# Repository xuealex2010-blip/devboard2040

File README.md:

# A custom devboard based on the RP2040
This is my very own design of a devboard, it is very similar to the Rasberry Pi Pico, I created it to learn more about microcontrollers, it is also my first design with a microcontroller.

## Overview
This devboard uses an RP2040, it exposes 28 total GPIO pins.

The devboard has 2 LEDs on it, a red one to signal the power connection, and a green one that can be controlled with GPIO 25.

It uses a USB-C connector instead off the Micro USB connector on the official one. And it has the necessary CC1 and CC2 resistors so it can be connected to a USB C port.

The external pins are also labeled, so that you don't always need to reference a pinout when working on projects.

Details with the source files can be previewed with KiCanvas: 

[https://kicanvas.org/?repo=https%3A%2F%2Fgithub.com%2Fxuealex2010-blip%2Fdevboard2040%2Ftree%2Fmain%2FPCB](url)

### Fabrication
The files necessary to manufacture your own version of this board can be found in the production folder, it has all of the necessary files and more, formatted for JLC PCB.
If you use another vendor, you may need to use the source files from the PCB folder to create your own production files.

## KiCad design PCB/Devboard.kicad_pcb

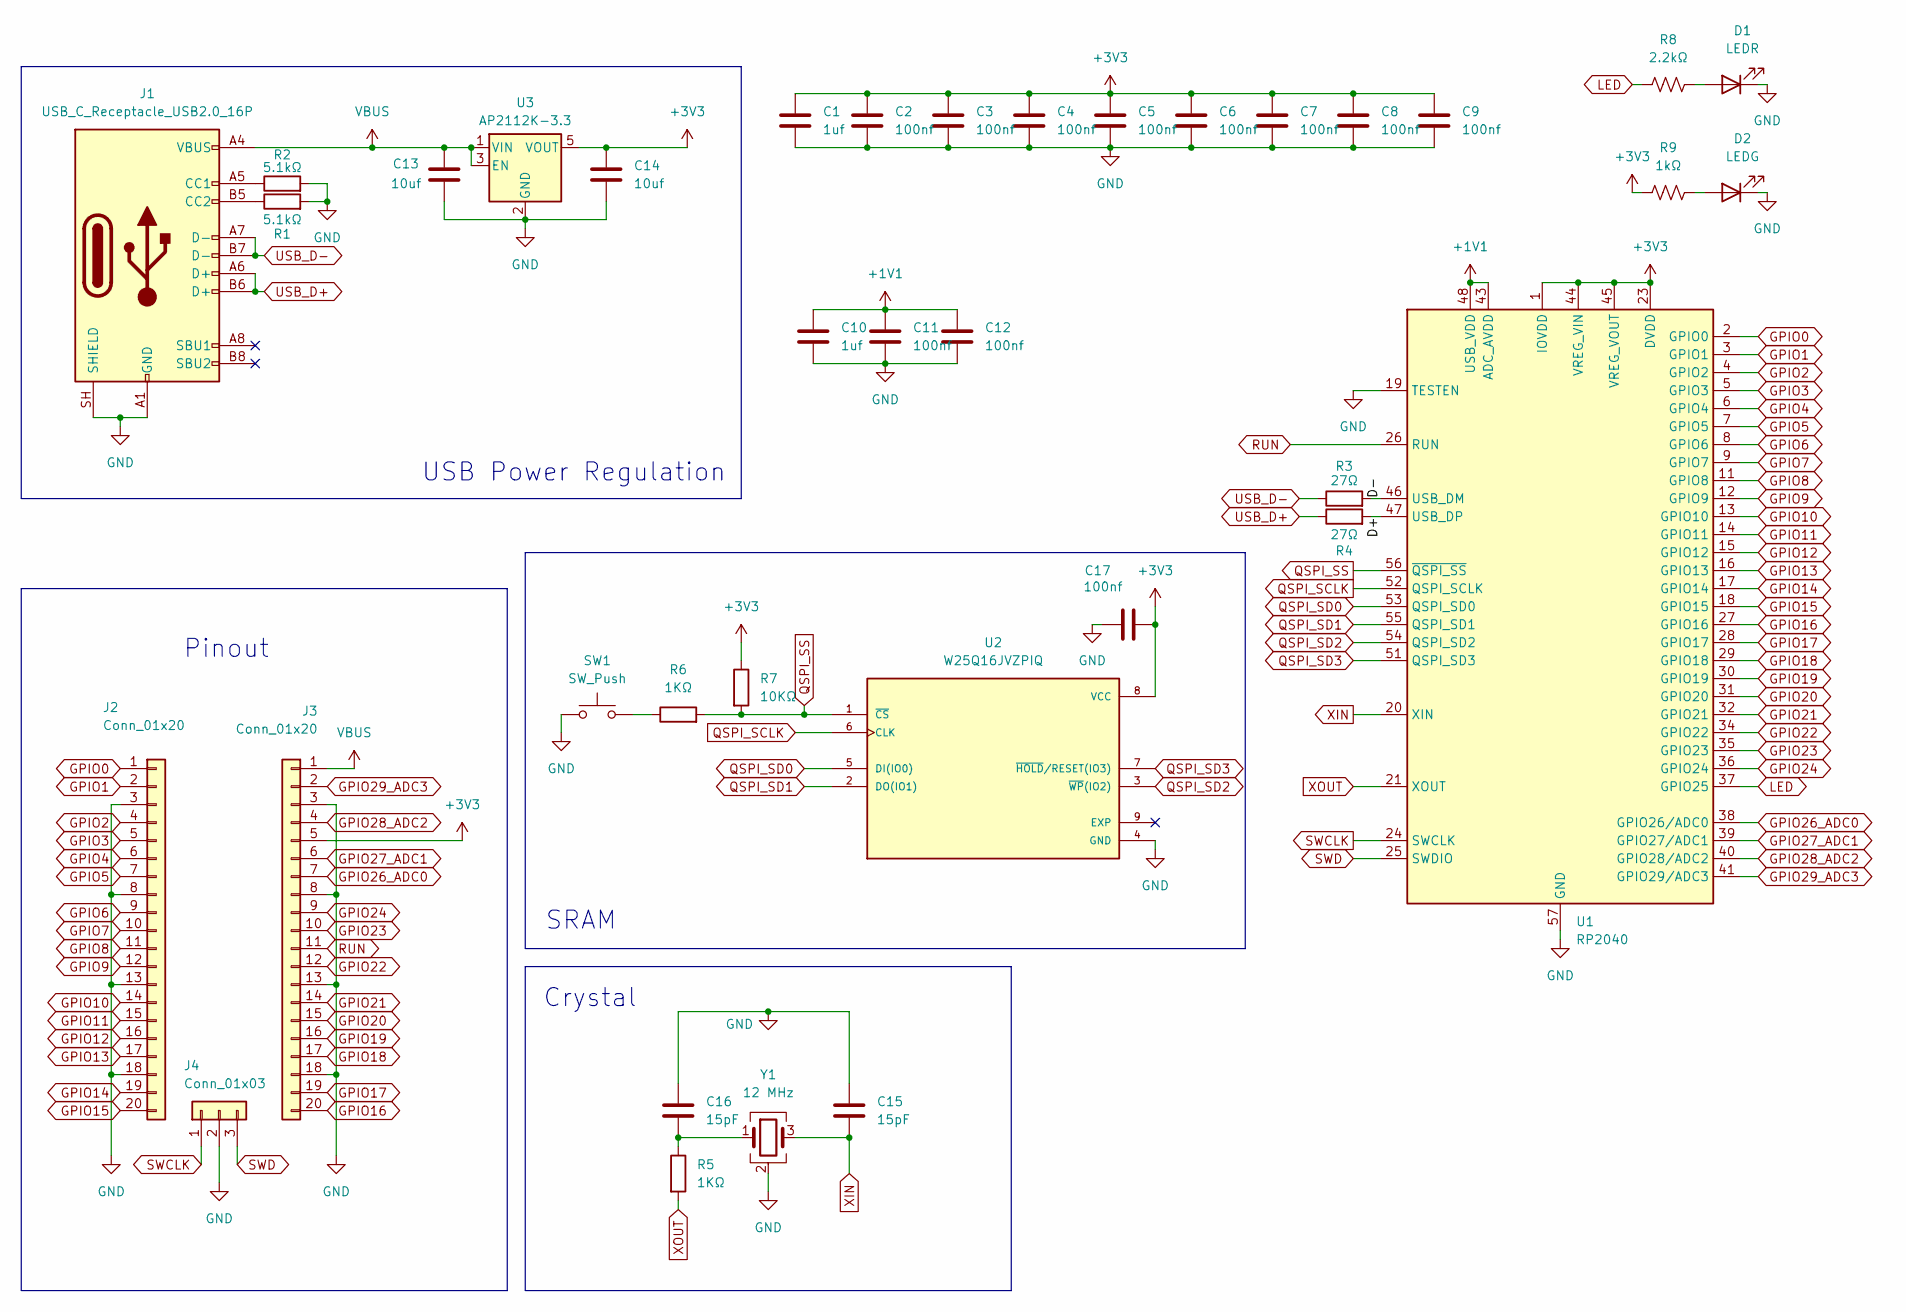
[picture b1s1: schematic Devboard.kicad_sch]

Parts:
C1, C10: 1uf; C_0402_1005Metric
C2, C3, C4, C5, C6, C7, C8, C9, C11, C12, C17: 100nf; C_0402_1005Metric
C13, C14: 10uf; C_0603_1608Metric
C15, C16: 15pF; C_0402_1005Metric
D1: LEDR; LED_0603_1608Metric
D2: LEDG; LED_0805_2012Metric
J1: USB_C_Receptacle_USB2.0_16P; USB_C_NEW(IDK)
J2, J3: Conn_01x20; PinHeader_1x20_P2.54mm_Vertical
J4: Conn_01x03; PinHeader_1x03_P2.54mm_Vertical
R1, R2: 5.1kΩ; R_0402_1005Metric
R3, R4: 27Ω; R_0402_1005Metric
R5, R6: 1KΩ; R_0402_1005Metric
R7: 10KΩ; R_0402_1005Metric
R8: 2.2kΩ; R_0402_1005Metric
R9: 1kΩ; R_0402_1005Metric
SW1: SW_Push; SW_Push_SPST_NO_Alps_SKRK
U1: RP2040; QFN-56-1EP_7x7mm_P0.4mm_EP3.2x3.2mm
U2: W25Q16JVZPIQ; Winbond_USON-8-1EP_3x2mm_P0.5mm_EP0.2x1.6mm
U3: AP2112K-3.3; SOT-23-5
Y1: 12 MHz; Crystal_SMD_3225-4Pin_3.2x2.5mm

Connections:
+1V1: C10.1, C11.1, C12.1, U1.43 (ADC_AVDD), U1.48 (USB_VDD)
+3V3: C1.1, C2.1, C3.1, C4.1, C5.1, C6.1, C7.1, C8.1, C9.1, C14.1, C17.1, J3.5, R7.1, R9.1, U1.1 (IOVDD), U1.10 (IOVDD), U1.22 (IOVDD), U1.23 (DVDD), U1.33 (IOVDD), U1.42 (IOVDD), U1.44 (VREG_VIN), U1.45 (VREG_VOUT), U1.49 (IOVDD), U1.50 (DVDD), U2.8 (VCC), U3.5 (VOUT)
/D+: R4.2, U1.47 (USB_DP)
/D-: R3.2, U1.46 (USB_DM)
GND: C1.2, C2.2, C3.2, C4.2, C5.2, C6.2, C7.2, C8.2, C9.2, C10.2, C11.2, C12.2, C13.2, C14.2, C15.1, C16.1, C17.2, D1.1 (K), D2.1 (K), J1.A1 (GND), J1.A12 (GND), J1.B1 (GND), J1.B12 (GND), J1.SH (SHIELD), J2.3, J2.8, J2.13, J2.18, J3.3, J3.8, J3.13, J3.18, J4.2, R1.2, R2.2, SW1.1, U1.19 (TESTEN), U1.57 (GND), U2.4 (GND), U3.2 (GND), Y1.2 (G), Y1.4 (G)
GPIO0: J2.1, U1.2 (GPIO0)
GPIO1: J2.2, U1.3 (GPIO1)
GPIO2: J2.4, U1.4 (GPIO2)
GPIO3: J2.5, U1.5 (GPIO3)
GPIO4: J2.6, U1.6 (GPIO4)
GPIO5: J2.7, U1.7 (GPIO5)
GPIO6: J2.9, U1.8 (GPIO6)
GPIO7: J2.10, U1.9 (GPIO7)
GPIO8: J2.11, U1.11 (GPIO8)
GPIO9: J2.12, U1.12 (GPIO9)
GPIO10: J2.14, U1.13 (GPIO10)
GPIO11: J2.15, U1.14 (GPIO11)
GPIO12: J2.16, U1.15 (GPIO12)
GPIO13: J2.17, U1.16 (GPIO13)
GPIO14: J2.19, U1.17 (GPIO14)
GPIO15: J2.20, U1.18 (GPIO15)
GPIO16: J3.20, U1.27 (GPIO16)
GPIO17: J3.19, U1.28 (GPIO17)
GPIO18: J3.17, U1.29 (GPIO18)
GPIO19: J3.16, U1.30 (GPIO19)
GPIO20: J3.15, U1.31 (GPIO20)
GPIO21: J3.14, U1.32 (GPIO21)
GPIO22: J3.12, U1.34 (GPIO22)
GPIO23: J3.10, U1.35 (GPIO23)
GPIO24: J3.9, U1.36 (GPIO24)
GPIO26_ADC0: J3.7, U1.38 (GPIO26/ADC0)
GPIO27_ADC1: J3.6, U1.39 (GPIO27/ADC1)
GPIO28_ADC2: J3.4, U1.40 (GPIO28/ADC2)
GPIO29_ADC3: J3.2, U1.41 (GPIO29/ADC3)
LED: R8.1, U1.37 (GPIO25)
unnamed: C16.2, R5.1, Y1.1
unnamed: D1.2 (A), R8.2
unnamed: D2.2 (A), R9.2
unnamed: J1.A5 (CC1), R2.1
unnamed: J1.B5 (CC2), R1.1
unnamed: R6.1, SW1.2
QSPI_SCLK: U1.52 (QSPI_SCLK), U2.6 (CLK)
QSPI_SD0: U1.53 (QSPI_SD0), U2.5 (DI(IO0))
QSPI_SD1: U1.55 (QSPI_SD1), U2.2 (DO(IO1))
QSPI_SD2: U1.54 (QSPI_SD2), U2.3 (~WP(IO2))
QSPI_SD3: U1.51 (QSPI_SD3), U2.7 (~HOLD/RESET(IO3))
QSPI_SS: R6.2, R7.2, U1.56 (~QSPI_SS), U2.1 (~CS)
RUN: J3.11, U1.26 (RUN)
SWCLK: J4.1, U1.24 (SWCLK)
SWD: J4.3, U1.25 (SWDIO)
USB_D+: J1.A6 (D+), J1.B6 (D+), R4.1
USB_D-: J1.A7 (D-), J1.B7 (D-), R3.1
VBUS: C13.1, J1.A4 (VBUS), J1.A9 (VBUS), J1.B4 (VBUS), J1.B9 (VBUS), J3.1, U3.1 (VIN), U3.3 (EN)
XIN: C15.2, U1.20 (XIN), Y1.3
XOUT: R5.2, U1.21 (XOUT)

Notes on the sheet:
USB Power Regulation
Crystal
Pinout
SRAM

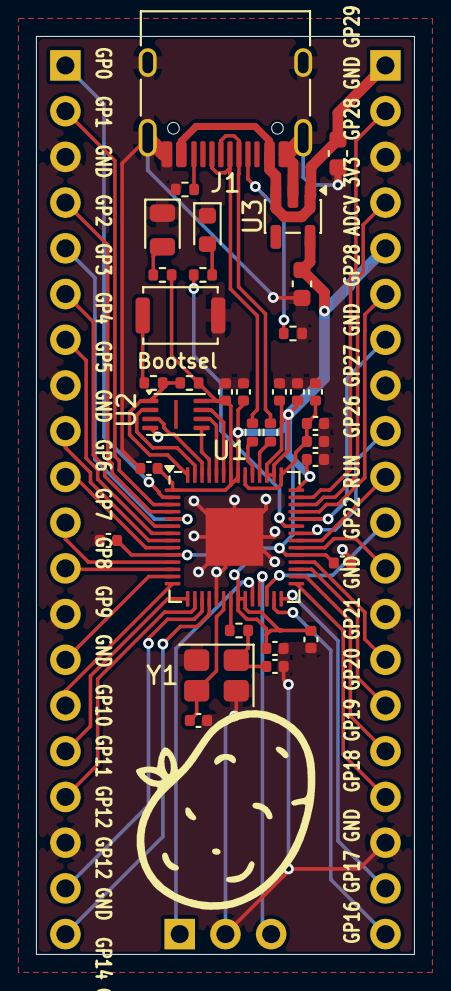
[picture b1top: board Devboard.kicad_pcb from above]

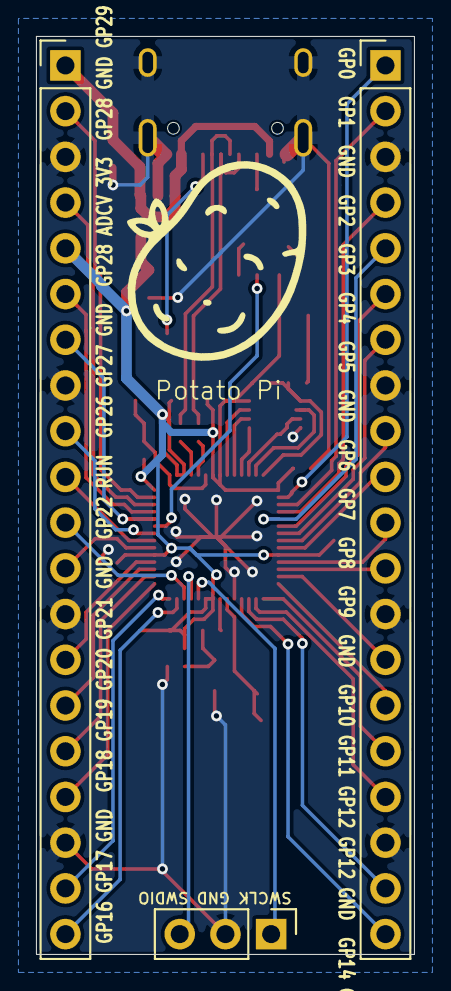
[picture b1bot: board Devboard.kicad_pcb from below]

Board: 2 copper layers, 21.0 x 51.0 mm, 37 parts (3 on the bottom side), 55 nets.

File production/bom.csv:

Designator,Footprint,Quantity,Value,LCSC Part #
"C1, C10",0402,2,1uf,
"C11, C12, C17, C2, C3, C4, C5, C6, C7, C8, C9",0402,11,100nf,
"C13, C14",0603,2,10uf,
"C15, C16",0402,2,15pF,
D1,0603,1,LEDR,
D2,0805,1,LEDG,
J1,USB_C_NEW(IDK),1,USB_C_Receptacle_USB2.0_16P,
"J2, J3",PinHeader_1x20_P2.54mm_Vertical,2,Conn_01x20,
J4,PinHeader_1x03_P2.54mm_Vertical,1,Conn_01x03,
"R1, R2",0402,2,5.1kΩ,
"R3, R4",0402,2,27Ω,
"R5, R6, R9",0402,3,1KΩ,
R7,0402,1,10KΩ,
R8,0402,1,2.2kΩ,
SW1,SW_Push_SPST_NO_Alps_SKRK,1,SW_Push,
U1,QFN-56-1EP_7x7mm_P0.4mm_EP3.2x3.2mm,1,RP2040,
U2,Winbond_USON-8-1EP_3x2mm_P0.5mm_EP0.2x1.6mm,1,W25Q16JVZPIQ,
U3,SOT-23-5,1,AP2112K-3.3,
Y1,Crystal_SMD_3225-4Pin_3.2x2.5mm,1,12 MHz,
